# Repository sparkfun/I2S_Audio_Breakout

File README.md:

SparkFun I2S Audio Breakout
========================================

[*I2S Audio Breakout (DEV-14809)*](https://www.sparkfun.com/products/14809)

The I2S Audio Breakout board uses the MAX98357A digital to analog converter (DAC), which converts I2S (not be confused with I2C) audio to an analog signal to drive speakers. The MAX98357A has a built in class D amplifier which can deliver up to 3.2W of power into a 4Ω load. To use this board, all you need is a speaker and a microcontroller that supports I2S. I2S is currently supported on our [SAMD21 Dev Breakout](https://www.sparkfun.com/products/13672), [SAMD21 Mini](https://www.sparkfun.com/products/13664), [ESP8266 Thing](https://www.sparkfun.com/products/13231), and [ESP32 Thing](https://www.sparkfun.com/products/13907) boards.

Repository Contents
-------------------

* **/Hardware** - Eagle design files (.brd, .sch)
* **/Production** - Production panel files (.brd)

Documentation
--------------
* **[Hookup Guide](https://learn.sparkfun.com/tutorials/i2s-audio-breakout-hookup-guide)** - Basic hookup guide for the I2S Audio Breakout.

License Information
-------------------

This product is _**open source**_! 

Please review the LICENSE.md file for license information. 

If you have any questions or concerns on licensing, please contact techsupport@sparkfun.com.

Distributed as-is; no warranty is given.

- Your friends at SparkFun.

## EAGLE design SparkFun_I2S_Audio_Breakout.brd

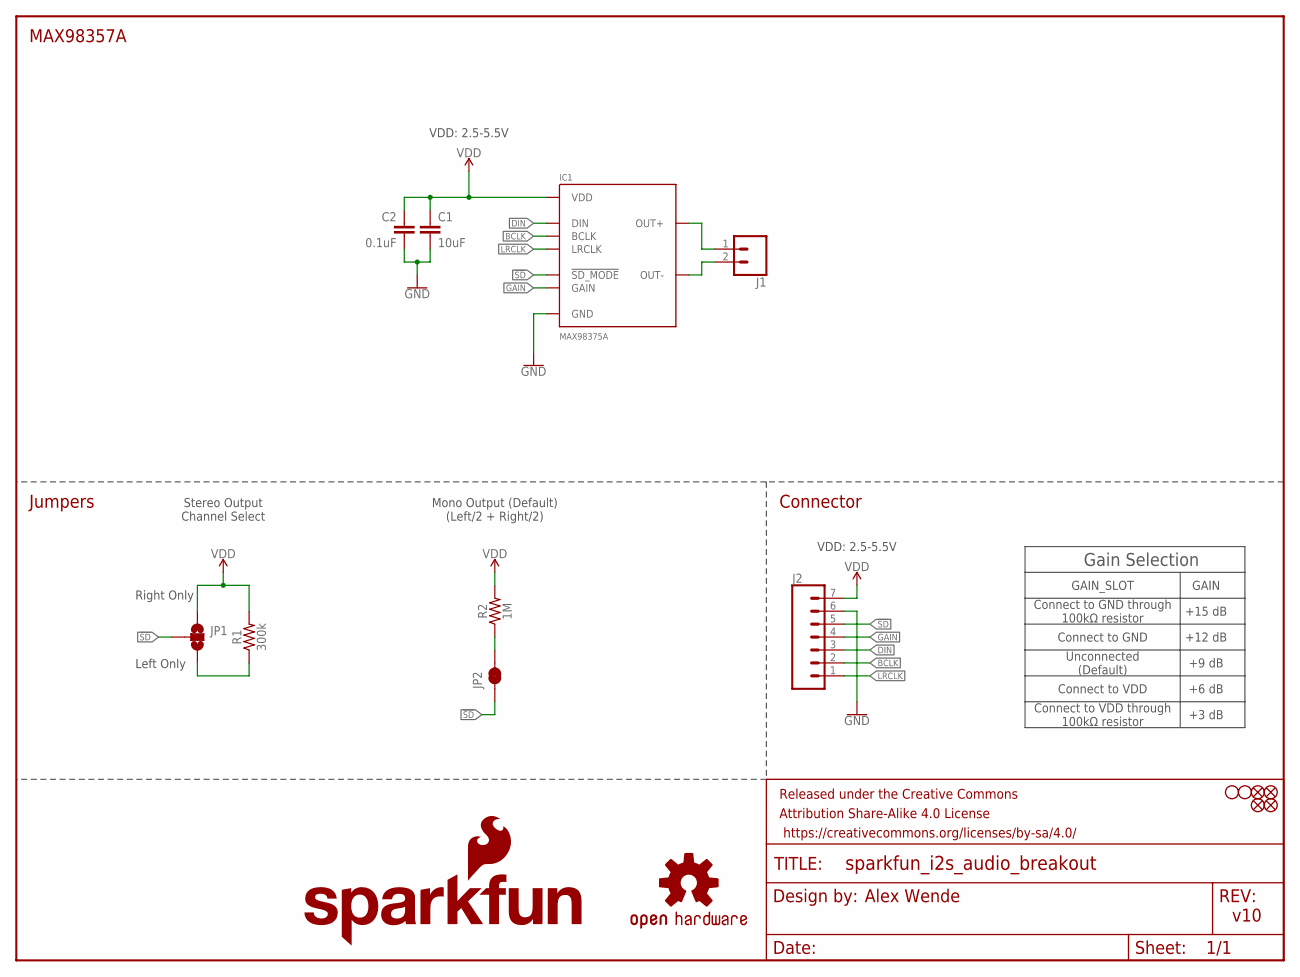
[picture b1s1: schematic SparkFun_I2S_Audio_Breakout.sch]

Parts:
C1: 10uF; 0805
C2: 0.1uF; 0603
FD1, FD2, FD3, FD4: FIDUCIALUFIDUCIAL; FIDUCIAL-MICRO
FRAME1: FRAME-LETTER; CREATIVE_COMMONS
H1, H2: STAND-OFF
IC1: MAX98375A; TQFN-16
J1: CONN_023.5MM-NO_SILK; SCREWTERMINAL-3.5MM-2-NS
J2: CONN_07NO_SILK; 1X07_NO_SILK
JP1: JUMPER-SMT_3_NO_NO-SILK; SMT-JUMPER_3_NO_NO-SILK
JP2: JUMPER-SMT_2_NC_TRACE_NO-SILK; SMT-JUMPER_2_NC_TRACE_NO-SILK
LOGO1: SFE_LOGO_NAME_FLAME.1_INCH; SFE_LOGO_NAME_FLAME_.1
LOGO2: OSHW-LOGOS; OSHW-LOGO-S
R1: 300k; 0603
R2: 1M; 0603

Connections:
!SD: IC1.P$4 (!SD_MODE), J2.5, JP1.2, JP2.1
BCLK: IC1.P$16 (BCLK), J2.2
DIN: IC1.P$1 (DIN), J2.3
GAIN: IC1.P$2 (GAIN), J2.4
GND: C1.2, C2.2, IC1.P$3 (GND), IC1.P$11 (GND), IC1.P$15 (GND), IC1.P$EP (GND), J2.6
LRCLK: IC1.P$14 (LRCLK), J2.1
unnamed: JP2.2, R2.1
unnamed: JP1.3, R1.1
OUT+: IC1.P$9 (OUT+), J1.1
OUT-: IC1.P$10 (OUT-), J1.2
VDD: C1.1, C2.1, IC1.P$7 (VDD), IC1.P$8 (VDD), J2.7, JP1.1, R1.2, R2.2

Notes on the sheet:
Alex Wende
v10
MAX98357A
Connector
Jumpers
Left Only
Right Only
Mono Output (Default) (Left/2 + Right/2)
Stereo Output Channel Select
Gain Selection
Connect to GND through 100kΩ resistor
Connect to GND
Unconnected (Default)
Connect to VDD
Connect to VDD through 100kΩ resistor
+15 dB
+12 dB
+9 dB
+6 dB
+3 dB
GAIN_SLOT
GAIN
VDD: 2.5-5.5V

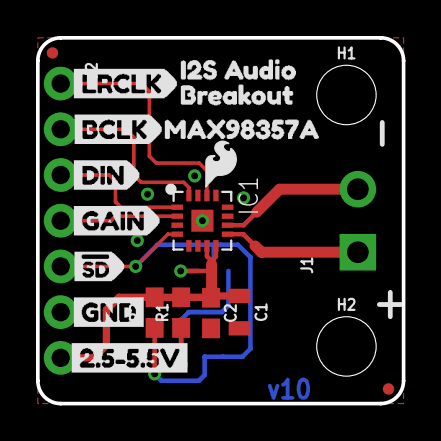
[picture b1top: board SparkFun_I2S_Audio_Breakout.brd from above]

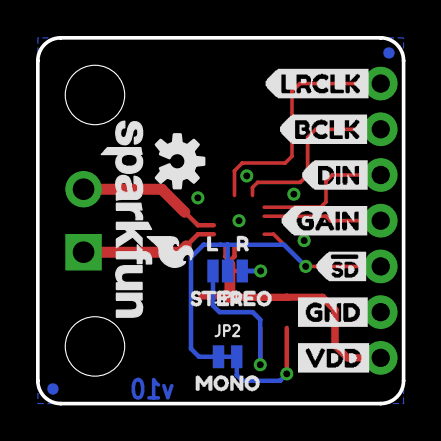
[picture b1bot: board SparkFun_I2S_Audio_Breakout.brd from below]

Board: 2 copper layers, 20.3 x 20.3 mm, 40 parts (17 on the bottom side), 11 nets.

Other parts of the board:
U$1: 2#5#5#5V13
U$2, U$23: GND9
U$3: #SD7
U$4: GAIN6
U$5: DIN5
U$6: BCLK4
U$7: LRCLK3
U$8: I2S_AUDIO0
U$9: BREAKOUT1
U$10: MAX98357A2
U$11: LRCLK0
U$12: BCLK1
U$13: DIN2
U$14: GAIN3
U$15: SFE_LOGO_FLAME_.1
U$16: MONO12
U$17: L10
U$18: R11
U$19: STEREO14
U$20: #SD4
U$22: VDD8

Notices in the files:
parts and their libraries:
SparkFun-IC-Amplifiers: Licensing: Creative Commons ShareAlike 4.0 International - https://creativecommons.org/licenses/by-sa/4.0
SparkFun-Aesthetics: Released under the Creative Commons Attribution Share-Alike 4.0 License
SparkFun-Aesthetics: https://creativecommons.org/licenses/by-sa/4.0
